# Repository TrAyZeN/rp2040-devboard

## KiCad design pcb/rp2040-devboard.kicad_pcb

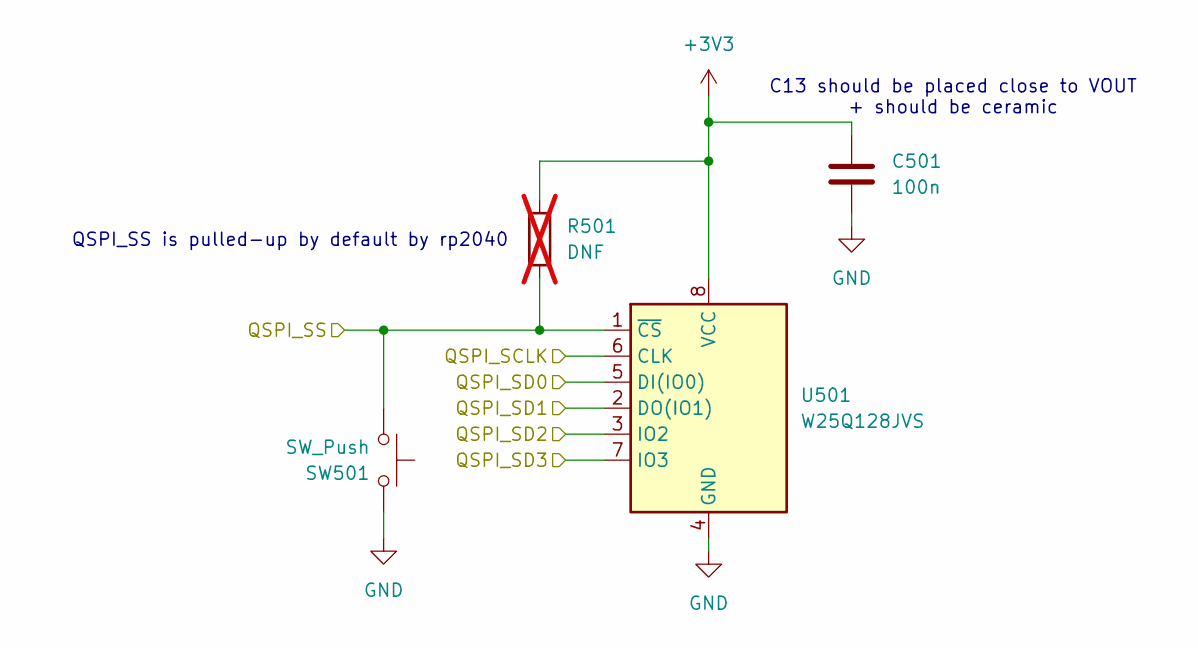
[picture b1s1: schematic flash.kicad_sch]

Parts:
C501: 100n; C_0603_1608Metric_Pad1.08x0.95mm_HandSolder
R501: DNF; R_0603_1608Metric_Pad0.98x0.95mm_HandSolder; not fitted
SW501: SW_Push; SW_SPST_EVPBV
U501: W25Q128JVS; SOIC-8_5.23x5.23mm_P1.27mm

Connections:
+3V3: C501.1, R501.1, U501.8 (VCC); also elsewhere on the board
/Flash/QSPI_SCLK: U501.6 (CLK); also elsewhere on the board
/Flash/QSPI_SD0: U501.5 (DI(IO0)); also elsewhere on the board
/Flash/QSPI_SD1: U501.2 (DO(IO1)); also elsewhere on the board
/Flash/QSPI_SD2: U501.3 (IO2); also elsewhere on the board
/Flash/QSPI_SD3: U501.7 (IO3); also elsewhere on the board
/Flash/QSPI_SS: R501.2, SW501.1, U501.1 (~CS); also elsewhere on the board
GND: C501.2, SW501.2, U501.4 (GND); also elsewhere on the board

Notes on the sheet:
QSPI_SS is pulled-up by default by rp2040
C13 should be placed close to VOUT + should be ceramic

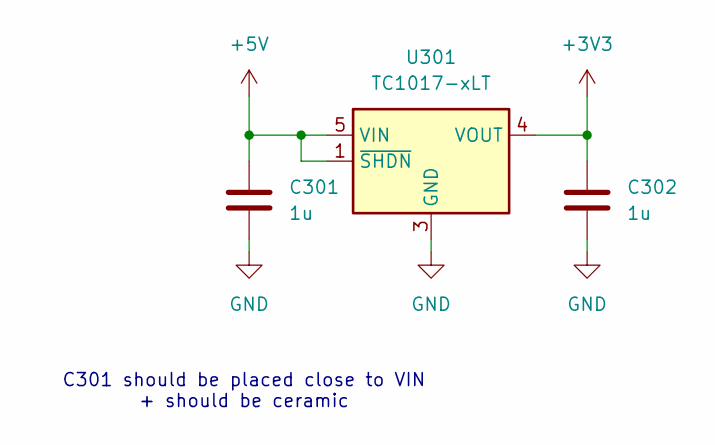
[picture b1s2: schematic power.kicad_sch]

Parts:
C301, C302: 1u; C_0603_1608Metric_Pad1.08x0.95mm_HandSolder
U301: TC1017-xLT; SOT-353_SC-70-5

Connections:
+3V3: C302.1, U301.4 (VOUT); also elsewhere on the board
+5V: C301.1, U301.1 (~SHDN), U301.5 (VIN); also elsewhere on the board
GND: C301.2, C302.2, U301.3 (GND); also elsewhere on the board

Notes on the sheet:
C301 should be placed close to VIN + should be ceramic

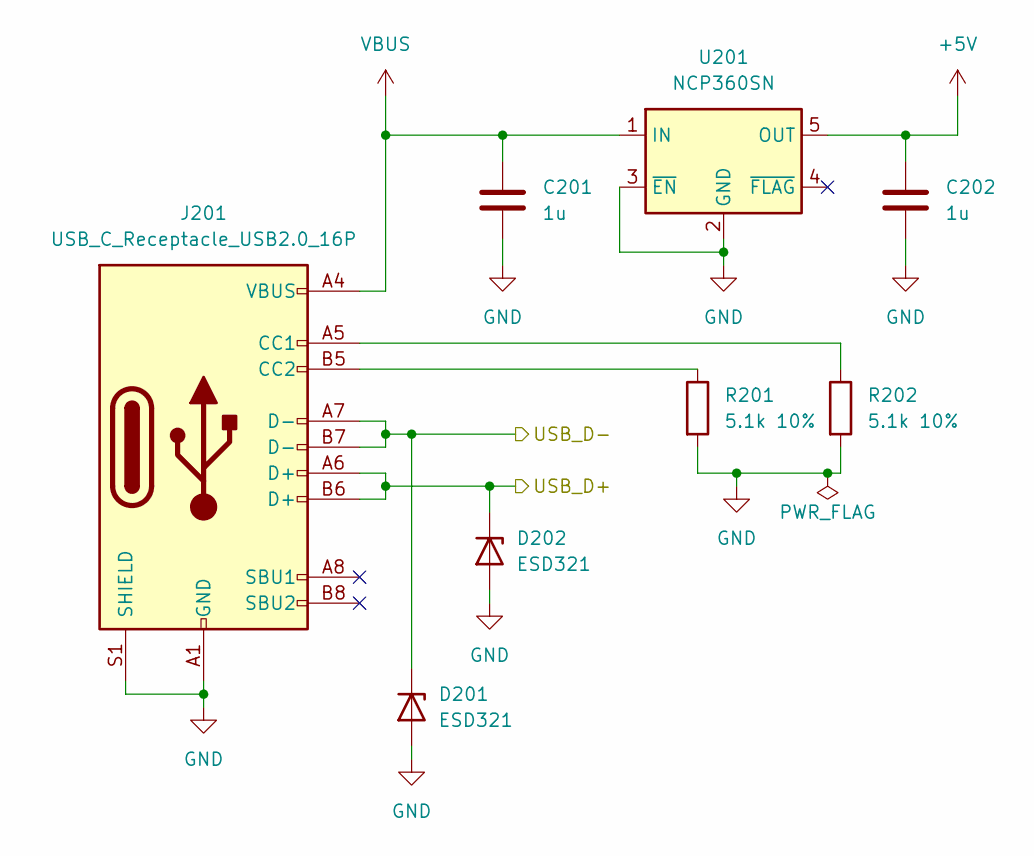
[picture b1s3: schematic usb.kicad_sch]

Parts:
C201, C202: 1u; C_0603_1608Metric_Pad1.08x0.95mm_HandSolder
D201, D202: ESD321; D_SOD-523
J201: USB_C_Receptacle_USB2.0_16P; USB_C_Receptacle_GCT_USB4105-xx-A_16P_TopMnt_Horizontal
R201, R202: 5.1k 10%; R_0603_1608Metric_Pad0.98x0.95mm_HandSolder
U201: NCP360SN; TSOP-5_1.65x3.05mm_P0.95mm

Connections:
+5V: C202.1, U201.5 (OUT); also elsewhere on the board
/USB/USB_D+: D202.1 (K), J201.A6 (D+), J201.B6 (D+); also elsewhere on the board
/USB/USB_D-: D201.1 (K), J201.A7 (D-), J201.B7 (D-); also elsewhere on the board
GND: C201.2, C202.2, D201.2 (A), D202.2 (A), J201.A1 (GND), J201.A12 (GND), J201.B1 (GND), J201.B12 (GND), J201.S1 (SHIELD), R201.2, R202.2, U201.2 (GND), U201.3 (~EN); also elsewhere on the board
unnamed: J201.A5 (CC1), R202.1
unnamed: J201.B5 (CC2), R201.1
VBUS: C201.1, J201.A4 (VBUS), J201.A9 (VBUS), J201.B4 (VBUS), J201.B9 (VBUS), U201.1 (IN)

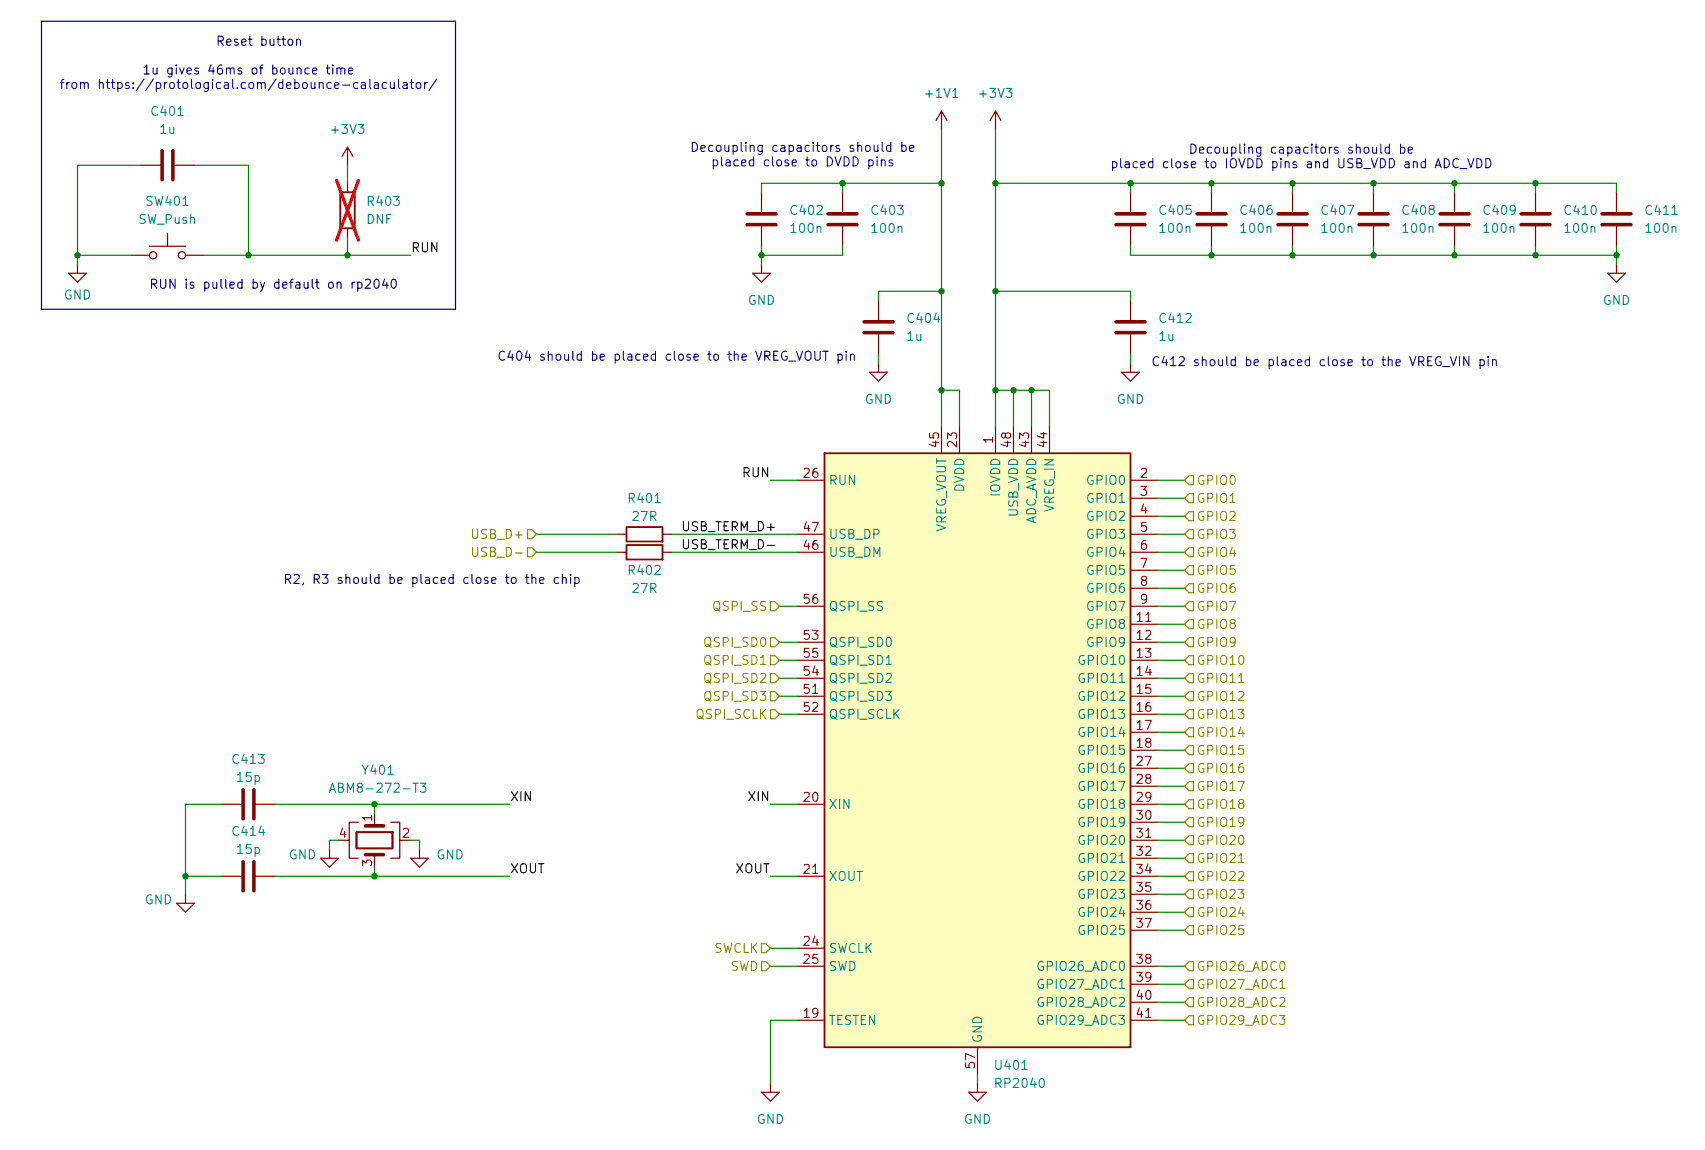
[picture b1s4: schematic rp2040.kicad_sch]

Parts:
C401, C404, C412: 1u; C_0603_1608Metric_Pad1.08x0.95mm_HandSolder
C402, C403, C405, C406, C407, C408, C409, C410, C411: 100n; C_0603_1608Metric_Pad1.08x0.95mm_HandSolder
C413, C414: 15p; C_0603_1608Metric_Pad1.08x0.95mm_HandSolder
R401, R402: 27R; R_0603_1608Metric_Pad0.98x0.95mm_HandSolder
R403: DNF; R_0603_1608Metric_Pad0.98x0.95mm_HandSolder; not fitted
SW401: SW_Push; SW_SPST_EVPBV
U401: RP2040; QFN-56-1EP_7x7mm_P0.4mm_EP3.2x3.2mm
Y401: ABM8-272-T3; Crystal_SMD_3225-4Pin_3.2x2.5mm

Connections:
+1V1: C402.1, C403.1, C404.1, U401.23 (DVDD), U401.45 (VREG_VOUT), U401.50 (DVDD)
+3V3: C405.1, C406.1, C407.1, C408.1, C409.1, C410.1, C411.1, C412.1, R403.1, U401.1 (IOVDD), U401.10 (IOVDD), U401.22 (IOVDD), U401.33 (IOVDD), U401.42 (IOVDD), U401.43 (ADC_AVDD), U401.44 (VREG_IN), U401.48 (USB_VDD), U401.49 (IOVDD); also elsewhere on the board
/Flash/QSPI_SCLK: U401.52 (QSPI_SCLK); also elsewhere on the board
/Flash/QSPI_SD0: U401.53 (QSPI_SD0); also elsewhere on the board
/Flash/QSPI_SD1: U401.55 (QSPI_SD1); also elsewhere on the board
/Flash/QSPI_SD2: U401.54 (QSPI_SD2); also elsewhere on the board
/Flash/QSPI_SD3: U401.51 (QSPI_SD3); also elsewhere on the board
/Flash/QSPI_SS: U401.56 (QSPI_SS); also elsewhere on the board
/IO/GPIO0: U401.2 (GPIO0); also elsewhere on the board
/IO/GPIO1: U401.3 (GPIO1); also elsewhere on the board
/IO/GPIO2: U401.4 (GPIO2); also elsewhere on the board
/IO/GPIO3: U401.5 (GPIO3); also elsewhere on the board
/IO/GPIO4: U401.6 (GPIO4); also elsewhere on the board
/IO/GPIO5: U401.7 (GPIO5); also elsewhere on the board
/IO/GPIO6: U401.8 (GPIO6); also elsewhere on the board
/IO/GPIO7: U401.9 (GPIO7); also elsewhere on the board
/IO/GPIO8: U401.11 (GPIO8); also elsewhere on the board
/IO/GPIO9: U401.12 (GPIO9); also elsewhere on the board
/IO/GPIO10: U401.13 (GPIO10); also elsewhere on the board
/IO/GPIO11: U401.14 (GPIO11); also elsewhere on the board
/IO/GPIO12: U401.15 (GPIO12); also elsewhere on the board
/IO/GPIO13: U401.16 (GPIO13); also elsewhere on the board
/IO/GPIO14: U401.17 (GPIO14); also elsewhere on the board
/IO/GPIO15: U401.18 (GPIO15); also elsewhere on the board
/IO/GPIO16: U401.27 (GPIO16); also elsewhere on the board
/IO/GPIO17: U401.28 (GPIO17); also elsewhere on the board
/IO/GPIO18: U401.29 (GPIO18); also elsewhere on the board
/IO/GPIO19: U401.30 (GPIO19); also elsewhere on the board
/IO/GPIO20: U401.31 (GPIO20); also elsewhere on the board
/IO/GPIO21: U401.32 (GPIO21); also elsewhere on the board
/IO/GPIO22: U401.34 (GPIO22); also elsewhere on the board
/IO/GPIO23: U401.35 (GPIO23); also elsewhere on the board
/IO/GPIO24: U401.36 (GPIO24); also elsewhere on the board
/IO/GPIO25: U401.37 (GPIO25); also elsewhere on the board
/IO/GPIO26_ADC0: U401.38 (GPIO26_ADC0); also elsewhere on the board
/IO/GPIO27_ADC1: U401.39 (GPIO27_ADC1); also elsewhere on the board
/IO/GPIO28_ADC2: U401.40 (GPIO28_ADC2); also elsewhere on the board
/IO/GPIO29_ADC3: U401.41 (GPIO29_ADC3); also elsewhere on the board
/IO/SWCLK: U401.24 (SWCLK); also elsewhere on the board
/IO/SWD: U401.25 (SWD); also elsewhere on the board
/USB/USB_D+: R401.1; also elsewhere on the board
/USB/USB_D-: R402.1; also elsewhere on the board
/rp2040/RUN: C401.2, R403.2, SW401.2, U401.26 (RUN)
/rp2040/USB_TERM_D+: R401.2, U401.47 (USB_DP)
/rp2040/USB_TERM_D-: R402.2, U401.46 (USB_DM)
/rp2040/XIN: C413.2, U401.20 (XIN), Y401.1
/rp2040/XOUT: C414.2, U401.21 (XOUT), Y401.3
GND: C401.1, C402.2, C403.2, C404.2, C405.2, C406.2, C407.2, C408.2, C409.2, C410.2, C411.2, C412.2, C413.1, C414.1, SW401.1, U401.19 (TESTEN), U401.57 (GND), Y401.2, Y401.4; also elsewhere on the board

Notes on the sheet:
C412 should be placed close to the VREG_VIN pin
Decoupling capacitors should be placed close to DVDD pins
Reset button
RUN is pulled by default on rp2040
R2, R3 should be placed close to the chip
Decoupling capacitors should be placed close to IOVDD pins and USB_VDD and ADC_VDD
1u gives 46ms of bounce time from https://protological.com/debounce-calaculator/
C404 should be placed close to the VREG_VOUT pin

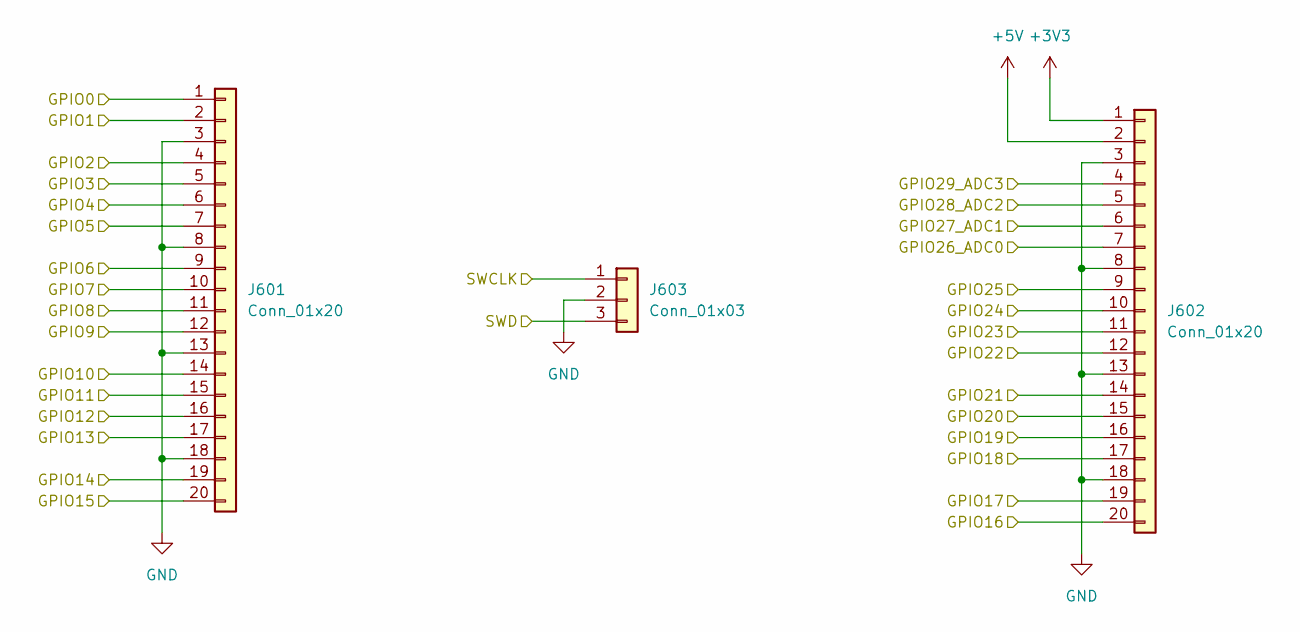
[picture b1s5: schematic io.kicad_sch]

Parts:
J601, J602: Conn_01x20; PinHeader_1x20_P2.54mm_Vertical
J603: Conn_01x03; PinHeader_1x03_P2.54mm_Vertical

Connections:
+3V3: J602.1; also elsewhere on the board
+5V: J602.2; also elsewhere on the board
/IO/GPIO0: J601.1; also elsewhere on the board
/IO/GPIO1: J601.2; also elsewhere on the board
/IO/GPIO2: J601.4; also elsewhere on the board
/IO/GPIO3: J601.5; also elsewhere on the board
/IO/GPIO4: J601.6; also elsewhere on the board
/IO/GPIO5: J601.7; also elsewhere on the board
/IO/GPIO6: J601.9; also elsewhere on the board
/IO/GPIO7: J601.10; also elsewhere on the board
/IO/GPIO8: J601.11; also elsewhere on the board
/IO/GPIO9: J601.12; also elsewhere on the board
/IO/GPIO10: J601.14; also elsewhere on the board
/IO/GPIO11: J601.15; also elsewhere on the board
/IO/GPIO12: J601.16; also elsewhere on the board
/IO/GPIO13: J601.17; also elsewhere on the board
/IO/GPIO14: J601.19; also elsewhere on the board
/IO/GPIO15: J601.20; also elsewhere on the board
/IO/GPIO16: J602.20; also elsewhere on the board
/IO/GPIO17: J602.19; also elsewhere on the board
/IO/GPIO18: J602.17; also elsewhere on the board
/IO/GPIO19: J602.16; also elsewhere on the board
/IO/GPIO20: J602.15; also elsewhere on the board
/IO/GPIO21: J602.14; also elsewhere on the board
/IO/GPIO22: J602.12; also elsewhere on the board
/IO/GPIO23: J602.11; also elsewhere on the board
/IO/GPIO24: J602.10; also elsewhere on the board
/IO/GPIO25: J602.9; also elsewhere on the board
/IO/GPIO26_ADC0: J602.7; also elsewhere on the board
/IO/GPIO27_ADC1: J602.6; also elsewhere on the board
/IO/GPIO28_ADC2: J602.5; also elsewhere on the board
/IO/GPIO29_ADC3: J602.4; also elsewhere on the board
/IO/SWCLK: J603.1; also elsewhere on the board
/IO/SWD: J603.3; also elsewhere on the board
GND: J601.3, J601.8, J601.13, J601.18, J602.3, J602.8, J602.13, J602.18, J603.2; also elsewhere on the board

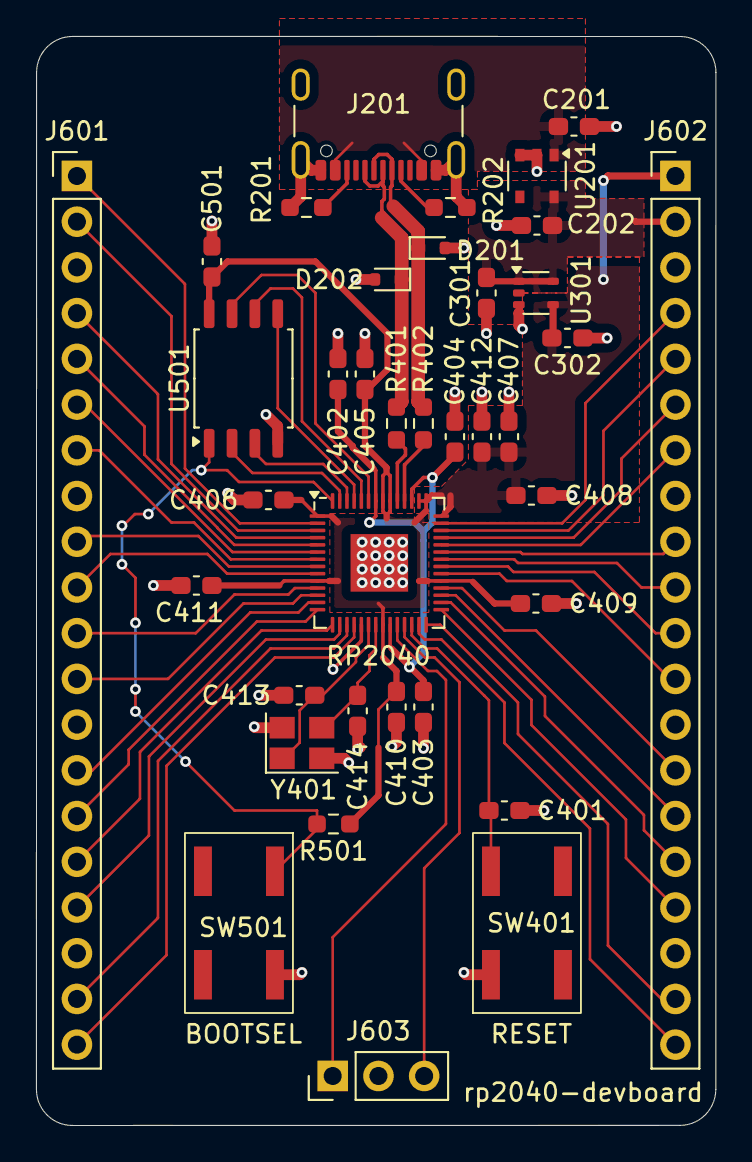
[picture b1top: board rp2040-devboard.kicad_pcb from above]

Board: 2 copper layers, 37.8 x 60.5 mm, 37 parts (0 on the bottom side), 52 nets.

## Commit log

2024-05-27 add schematic
2024-05-28 add footprints
2024-06-09 add footprints + expose grounds and power on pins
2024-06-09 wip pcb placement
2024-06-23 change footprint
2024-07-13 finish routing
2024-08-13 mirror back silkscreen
2024-08-23 add debouncing capacitor value and dnp pull up
2024-08-23 add interactive bom config
